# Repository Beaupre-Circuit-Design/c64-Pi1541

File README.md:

# Pi1541-Hat

# Introduction

An open-source Raspberry-Pi Hat for the [Pi1541 firmware](https://cbm-pi1541.firebaseapp.com/). The Hat is divided into two small PCB, the mainboard with the connectors and support logic, and the control board.  They can be assembled together in one unit, or separatly to fit your choice of enclosure.

# Compatibility

The Hat should be compatible with all 40-pins Raspberry Pi supported by the Pi1541 project. That said, i've only tested it with a Raspberry-Pi Zero 2W.

# Configuration

## Rasperry-Pi Zero/2/3.

Follow the instructions of the official firmware. Once your SD created, change the following lines in the file 'options.txt':

    // Uncomment splitIECLines by uncommenting this line. .
	splitIECLines = 1
	// Enable the LCD Display by uncommenting this line. 
	LCDName = ssd1306_128x64
	// Enable KeyboardBrowseLCDScreen by uncommenting theses lines.
	KeyboardBrowseLCDScreen = 1
	i2cBusMaster = 0
	// Disabling GraphIEC for more stability and compatibility with fastloaders by commenting this line.
	//GraphIEC = 1

## Rasperry-Pi Zero 2W.

Follow the instructions of the [c64-Pi1541-Zero2W-Firmware]([Firmware/](https://github.com/Beaupre-Circuit-Design/c64-Pi1541-Zero2W-Firmware)) Github repository.

# Components and assembly

[Gerbers files](Gerbers/) and SMD assembly files are available for uploading to your prefered manufacturer (I personnally use JLCPCB).  The mainboard use SMT parts (except for the headers) while the control board use through-hole components. Refer to the [Bill of Materials](Pi1541-BOM.xlsx) Excel sheet for a complete list of needed components.

# Licence

This work is licensed under the Creative Commons Attribution-NonCommercial-ShareAlike 4.0 International License. To view a copy of this license, visit http://creativecommons.org/licenses/by-nc-sa/4.0/ or send a letter to Creative Commons, PO Box 1866, Mountain View, CA 94042, USA.

# Revision History

|Revision  |Description                    |
|:--------:|-------------------------------|
|1.0       |Initial prototype              |

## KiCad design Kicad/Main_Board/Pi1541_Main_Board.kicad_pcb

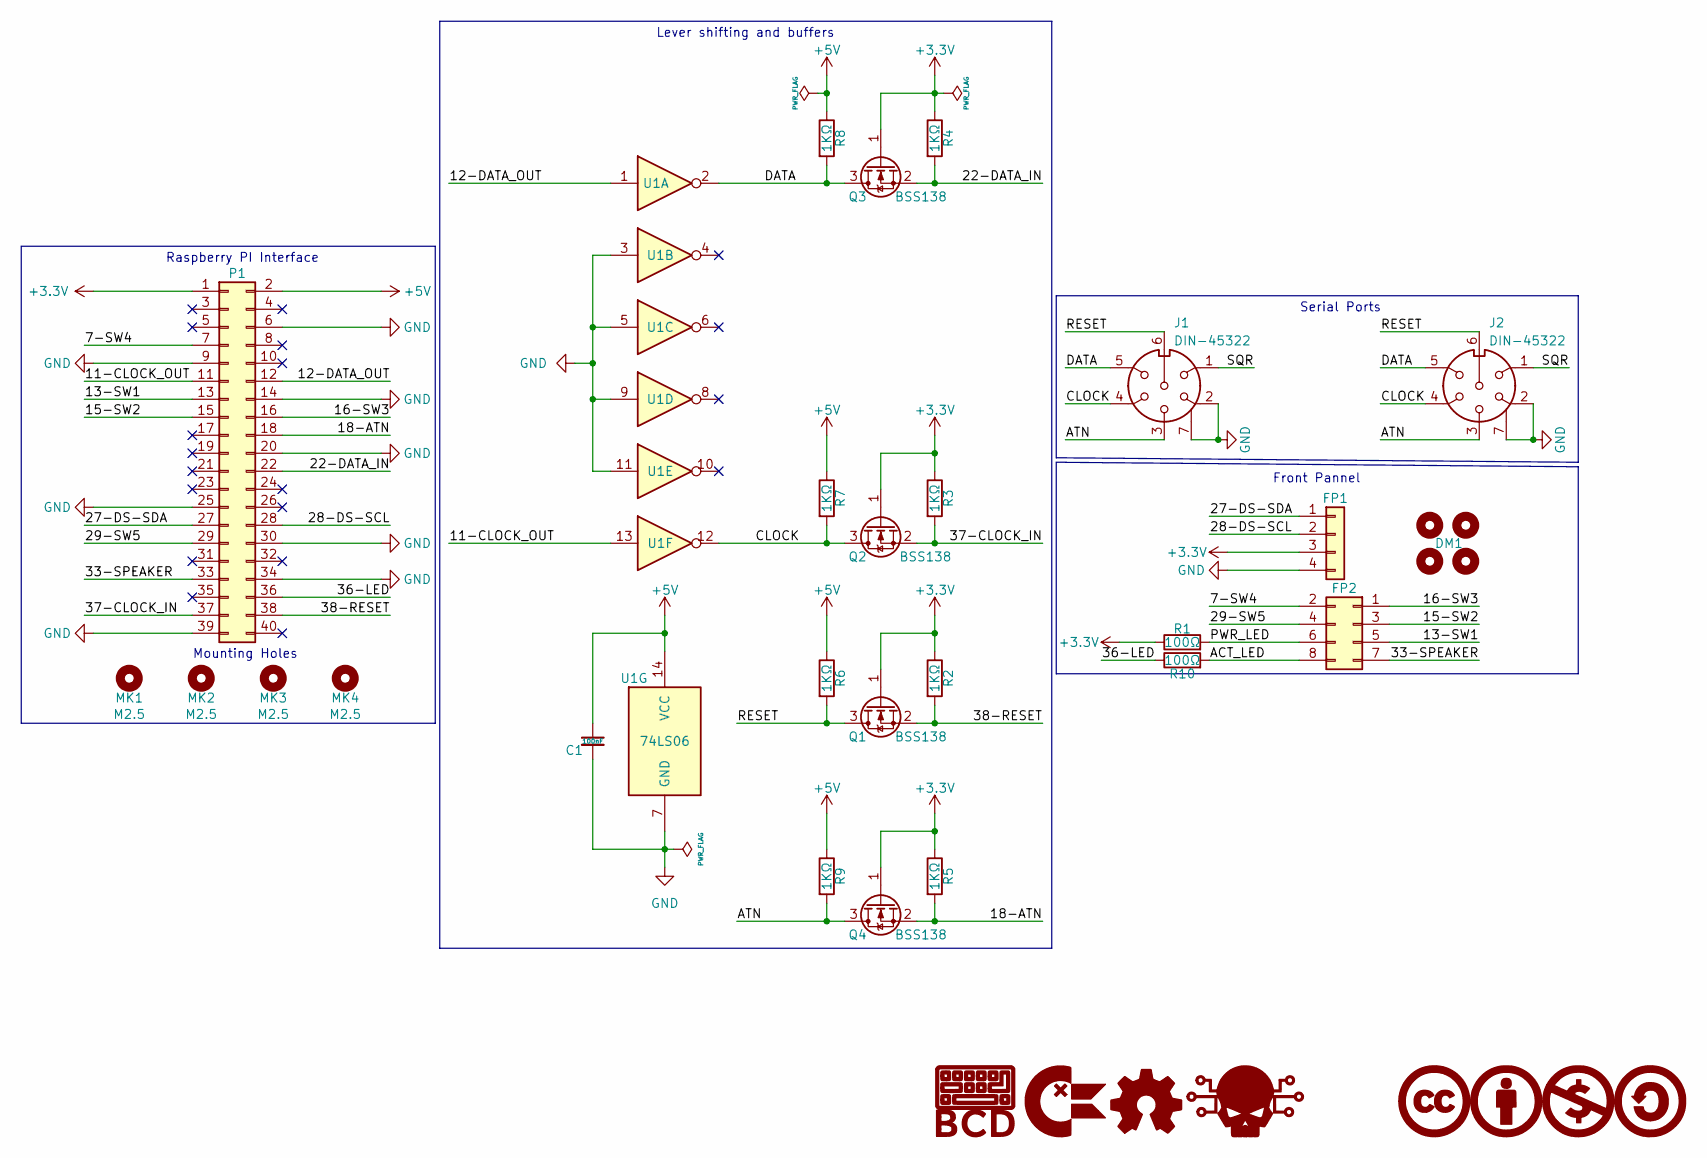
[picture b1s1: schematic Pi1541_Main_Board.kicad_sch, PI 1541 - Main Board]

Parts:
C1: 100nF; C_0805_2012Metric; Mfr.Part CL21C101JBANNNC; LCSC C1790
DM1: 128x64_I2C_OLED_Mounting_Holes; 128x64 I2C OLED Mounting Holes
FP1: Conn_01x04_Counter_Clockwise; PinSocket_1x04_P2.54mm_Vertical; Mfr.Part C2718488; LCSC C2718488
FP2: Conn_02x04_Counter_Clockwise; PinSocket_2x04_P2.54mm_Vertical; Mfr.Part B-2200S08P-B120; LCSC C124422
G1: BCD_Logo; BCD_Logo_5mm
G2: ChickenLips; ChickenLips_5mm
G3: OpenSource_Hardware; Open_Source_Hardware_5mm
G4: Skull; Skull_5mm
G5: CreativeCommons; CreativeCommons_5mm
G6: CreativeCommons_Attribution; CreativeCommons_Attribution_5mm
G7: CreativeCommons_NonCommercial; CreativeCommons_NonCommercial_5mm
G8: CreativeCommons_ShareAlike; CreativeCommons_ShareAlike_5mm
J1, J2: DIN-45322; DIN_45322
MK1, MK2, MK3, MK4: M2.5; MountingHole_2.7mm_M2.5
P1: Conn_02x20_Odd_Even; PinSocket_2x20_P2.54mm_Vertical; Mfr.Part C50982; LCSC C50982
Q1, Q2, Q3, Q4: BSS138; SOT-23; Mfr.Part BSS138; LCSC C112239
R1, R10: 100Ω; R_0805_2012Metric; Mfr.Part 0805W8F1000T5E; LCSC C17408
R2, R3, R4, R5, R6, R7, R8, R9: 1KΩ; R_0805_2012Metric; Mfr.Part 0805W8F1001T5E; LCSC C17513
U1: 74LS06; SOIC-14_3.9x8.7mm_P1.27mm; Mfr.Part SN74LS06DR; LCSC C113682

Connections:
+3V3: FP1.3, P1.1, Q1.1 (G), Q2.1 (G), Q3.1 (G), Q4.1 (G), R1.1, R2.1, R3.1, R4.1, R5.1
+5V: C1.1, P1.2, R6.1, R7.1, R8.1, R9.1, U1.14 (VCC)
/7-SW4: FP2.2, P1.7
/11-CLOCK_OUT: P1.11, U1.13
/12-DATA_OUT: P1.12, U1.1
/13-SW1: FP2.5, P1.13
/15-SW2: FP2.3, P1.15
/16-SW3: FP2.1, P1.16
/18-ATN: P1.18, Q4.2 (S), R5.2
/22-DATA_IN: P1.22, Q3.2 (S), R4.2
/27-DS-SDA: FP1.1, P1.27
/28-DS-SCL: FP1.2, P1.28
/29-SW5: FP2.4, P1.29
/33-SPEAKER: FP2.7, P1.33
/36-LED: P1.36, R10.1
/37-CLOCK_IN: P1.37, Q2.2 (S), R3.2
/38-RESET: P1.38, Q1.2 (S), R2.2
/ACT_LED: FP2.8, R10.2
/ATN: J1.3, J2.3, Q4.3 (D), R9.2
/CLOCK: J1.4, J2.4, Q2.3 (D), R7.2, U1.12
/DATA: J1.5, J2.5, Q3.3 (D), R8.2, U1.2
/PWR_LED: FP2.6, R1.2
/RESET: J1.6, J2.6, Q1.3 (D), R6.2
/SQR: J1.1, J2.1
GND: C1.2, FP1.4, J1.2, J1.7, J2.2, J2.7, P1.6, P1.9, P1.14, P1.20, P1.25, P1.30, P1.34, P1.39, U1.3, U1.5, U1.7 (GND), U1.9, U1.11

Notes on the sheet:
Front Pannel
Serial Ports
Mounting Holes
Raspberry PI Interface
Lever shifting and buffers

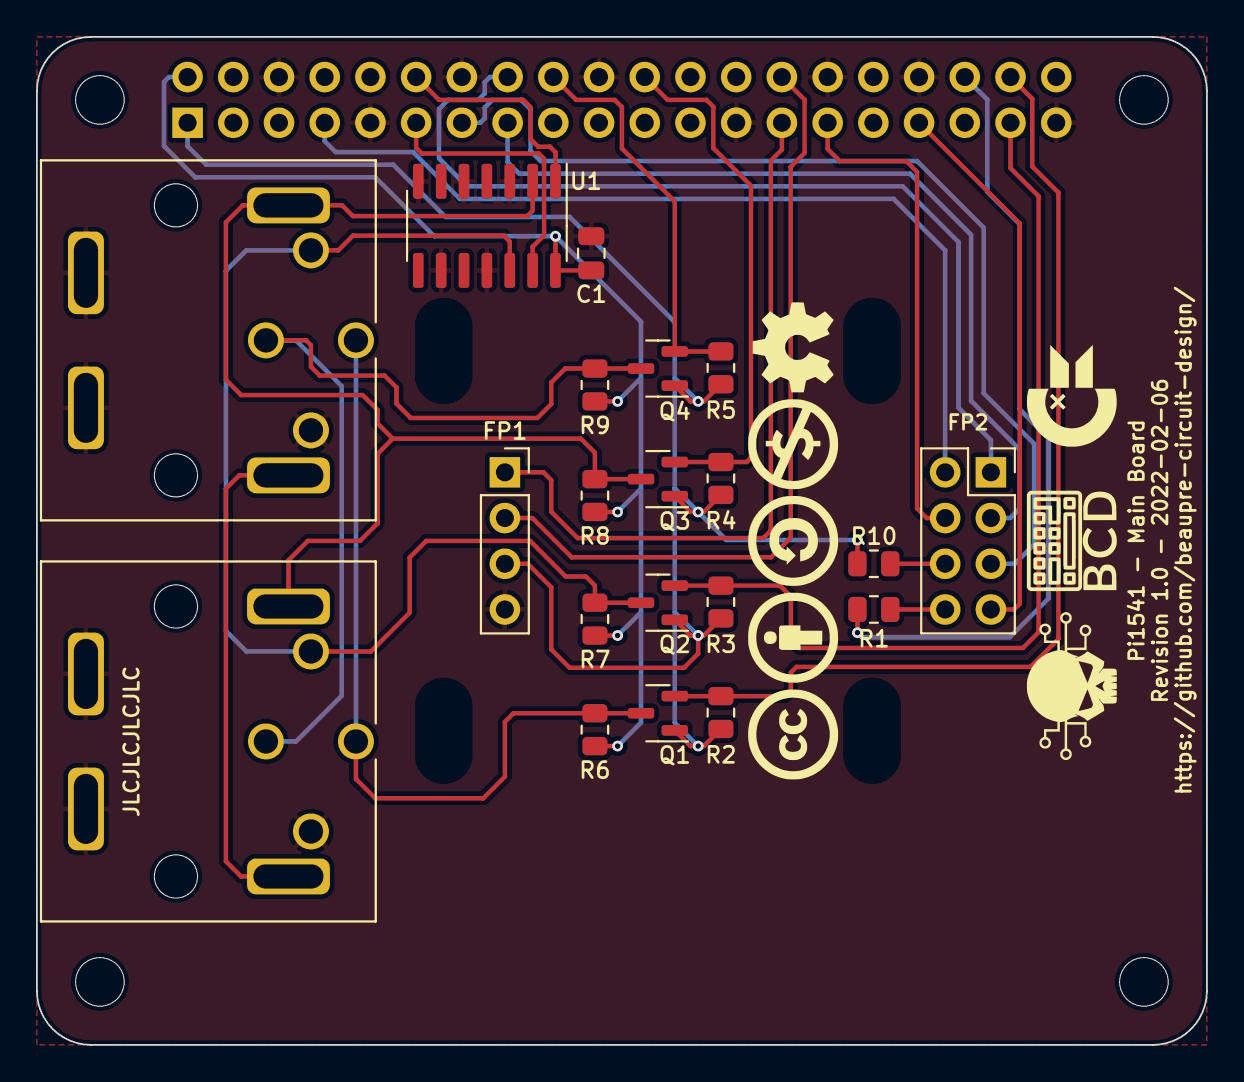
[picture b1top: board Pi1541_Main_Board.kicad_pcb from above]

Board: 2 copper layers, 65.0 x 56.0 mm, 34 parts (1 on the bottom side), 25 nets.

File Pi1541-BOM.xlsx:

Ref | Value | Footprint | Datasheet | Manufacturer | Mfr.Part | LCSC | Digikey | AliExpress | Notes
C1 | 100nF | Capacitor_SMD:C_0805_2012Metric | https://datasheet.lcsc.com/lcsc/1810241824_Samsung-Electro-M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 | Samsung Electro-Mechanics | CL21C101JBANNNC | C1790 | 1276-1014-1-ND
FP1 | Conn_01x04_Counter_Clockwise | Connector_PinSocket_2.54mm:PinSocket_1x04_P2.54mm_Vertical | https://datasheet.lcsc.com/lcsc/2103011236_BOOMELE-Boom-Prec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 | Boom Precision Elec | C2718488 | C2718488 | S7037-ND
FP2 | Conn_02x04_Counter_Clockwise | Connector_PinSocket_2.54mm:PinSocket_2x04_P2.54mm_Vertical | https://datasheet.lcsc.com/lcsc/1810221610_Ckmtw-Shenzhen-Ca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 | Shenzhen Cankemeng | B-2200S08P-B120 | C124422 | S7107-ND
J1 | DIN-45322 | DIN_45322:DIN_45322 | https://www.aliexpress.com/item/1005001265863686.html | AliExpress |  |  |  | 1005001265863680
J2 | DIN-45322 | DIN_45322:DIN_45322 | https://www.aliexpress.com/item/1005001265863686.html | AliExpress |  |  |  | 1005001265863680
P1 | Conn_02x20_Odd_Even | Connector_PinSocket_2.54mm:PinSocket_2x20_P2.54mm_Vertical | https://datasheet.lcsc.com/lcsc/1811111512_BOOMELE-Boom-Prec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 | Boom Precision Elec | C50982 | C50982 | S7123-ND
Q1 | BSS138 | Package_TO_SOT_SMD:SOT-23 | https://datasheet.lcsc.com/lcsc/1811101310_Shikues-BSS138_C1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 | Shikues | BSS138 | C112239 | BSS138CT-ND
Q2 | BSS138 | Package_TO_SOT_SMD:SOT-23 | https://datasheet.lcsc.com/lcsc/1811101310_Shikues-BSS138_C1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 | Shikues | BSS138 | C112239 | BSS138CT-ND
Q3 | BSS138 | Package_TO_SOT_SMD:SOT-23 | https://datasheet.lcsc.com/lcsc/1811101310_Shikues-BSS138_C1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 | Shikues | BSS138 | C112239 | BSS138CT-ND
Q4 | BSS138 | Package_TO_SOT_SMD:SOT-23 | https://datasheet.lcsc.com/lcsc/1811101310_Shikues-BSS138_C1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 | Shikues | BSS138 | C112239 | BSS138CT-ND
R1 | 100Ω | Resistor_SMD:R_0805_2012Metric | https://datasheet.lcsc.com/lcsc/2110251730_UNI-ROYAL-Uniroya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 | UNI-ROYAL(Uniroyal Elec) | 0805W8F1000T5E | C17408 | 311-100CRCT-ND
R2 | 1KΩ | Resistor_SMD:R_0805_2012Metric | https://datasheet.lcsc.com/lcsc/2110251730_UNI-ROYAL-Uniroya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 | UNI-ROYAL(Uniroyal Elec) | 0805W8F1001T5E | C17513 | 311-1.00KCRCT-ND
R3 | 1KΩ | Resistor_SMD:R_0805_2012Metric | https://datasheet.lcsc.com/lcsc/2110251730_UNI-ROYAL-Uniroya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 | UNI-ROYAL(Uniroyal Elec) | 0805W8F1001T5E | C17513 | 311-1.00KCRCT-ND
R4 | 1KΩ | Resistor_SMD:R_0805_2012Metric | https://datasheet.lcsc.com/lcsc/2110251730_UNI-ROYAL-Uniroya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 | UNI-ROYAL(Uniroyal Elec) | 0805W8F1001T5E | C17513 | 311-1.00KCRCT-ND
R5 | 1KΩ | Resistor_SMD:R_0805_2012Metric | https://datasheet.lcsc.com/lcsc/2110251730_UNI-ROYAL-Uniroya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 | UNI-ROYAL(Uniroyal Elec) | 0805W8F1001T5E | C17513 | 311-1.00KCRCT-ND
R6 | 1KΩ | Resistor_SMD:R_0805_2012Metric | https://datasheet.lcsc.com/lcsc/2110251730_UNI-ROYAL-Uniroya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 | UNI-ROYAL(Uniroyal Elec) | 0805W8F1001T5E | C17513 | 311-1.00KCRCT-ND
R7 | 1KΩ | Resistor_SMD:R_0805_2012Metric | https://datasheet.lcsc.com/lcsc/2110251730_UNI-ROYAL-Uniroya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 | UNI-ROYAL(Uniroyal Elec) | 0805W8F1001T5E | C17513 | 311-1.00KCRCT-ND
R8 | 1KΩ | Resistor_SMD:R_0805_2012Metric | https://datasheet.lcsc.com/lcsc/2110251730_UNI-ROYAL-Uniroya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 | UNI-ROYAL(Uniroyal Elec) | 0805W8F1001T5E | C17513 | 311-1.00KCRCT-ND
R9 | 1KΩ | Resistor_SMD:R_0805_2012Metric | https://datasheet.lcsc.com/lcsc/2110251730_UNI-ROYAL-Uniroya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 | UNI-ROYAL(Uniroyal Elec) | 0805W8F1001T5E | C17513 | 311-1.00KCRCT-ND
R10 | 100Ω | Resistor_SMD:R_0805_2012Metric | https://datasheet.lcsc.com/lcsc/2110251730_UNI-ROYAL-Uniroya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 | UNI-ROYAL(Uniroyal Elec) | 0805W8F1000T5E | C17408 | 311-100CRCT-ND
U1 | 74LS06 | Package_SO:SOIC-14_3.9x8.7mm_P1.27mm | https://datasheet.lcsc.com/lcsc/1810151621_Texas-Instruments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 | Texas Instruments | SN74LS06DR | C113682 | 296-14876-1-ND

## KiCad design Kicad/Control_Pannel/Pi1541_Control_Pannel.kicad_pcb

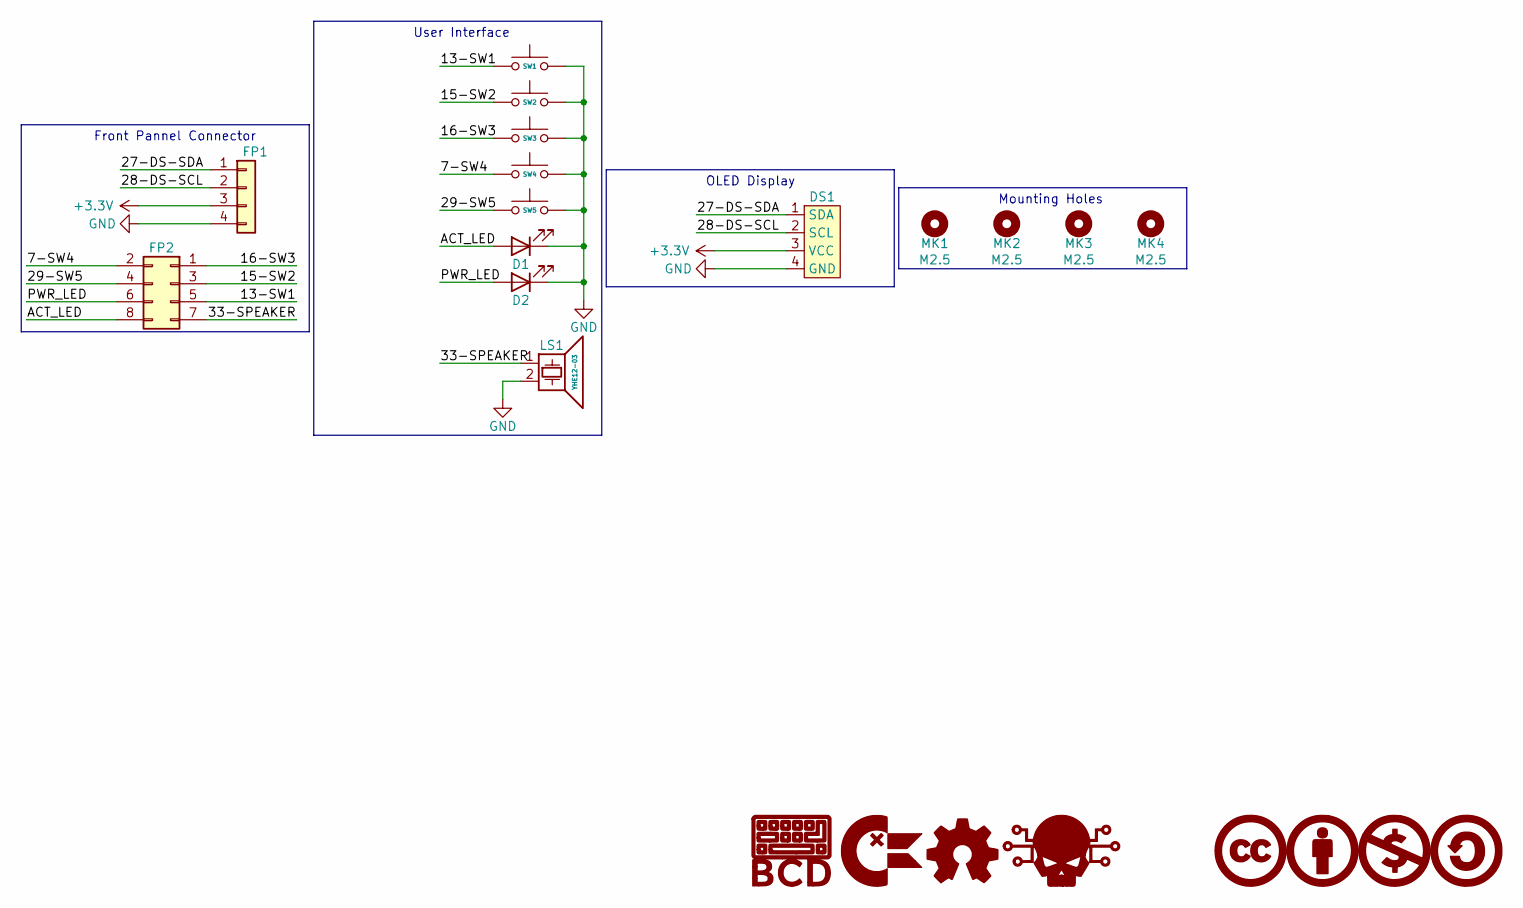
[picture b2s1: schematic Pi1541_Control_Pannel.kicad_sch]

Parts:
D1: RED LED; LED_D5.0mm; Mfr.Part 333-2SURD/S530-A3; LCSC C87271
D2: GREEN LED; LED_D5.0mm; Mfr.Part 333-2SYGD/S530-E2; LCSC C88163
DS1: 128x64_I2C_OLED_Display; 128x64 I2C OLED Display
FP1: Conn_01x04_Counter_Clockwise; PinHeader_1x04_P2.54mm_Vertical; Mfr.Part B-2100S04P-A110; LCSC C124378
FP2: Conn_02x04_Counter_Clockwise; PinHeader_2x04_P2.54mm_Vertical; Mfr.Part B-2100S08P-B110; LCSC C124386
G1: BCD_Logo; BCD_Logo_5mm
G2: ChickenLips; ChickenLips_5mm
G3: OpenSource_Hardware; Open_Source_Hardware_5mm
G4: Skull; Skull_5mm
G5: CreativeCommons; CreativeCommons_5mm
G6: CreativeCommons_Attribution; CreativeCommons_Attribution_5mm
G7: CreativeCommons_NonCommercial; CreativeCommons_NonCommercial_5mm
G8: CreativeCommons_ShareAlike; CreativeCommons_ShareAlike_5mm
LS1: YHE12-03; Buzzer_12x9.5RM7.6
MK1, MK2, MK3, MK4: M2.5; MountingHole_2.7mm_M2.5
SW1, SW2, SW3, SW4, SW5: SW_Push; SW_PUSH_6mm

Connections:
+3V3: DS1.3 (VCC), FP1.3
/7-SW4: FP2.2, SW4.1
/13-SW1: FP2.5, SW1.1
/15-SW2: FP2.3, SW2.1
/16-SW3: FP2.1, SW3.1
/27-DS-SDA: DS1.1 (SDA), FP1.1
/28-DS-SCL: DS1.2 (SCL), FP1.2
/29-SW5: FP2.4, SW5.1
/33-SPEAKER: FP2.7, LS1.1
/ACT_LED: D1.2 (A), FP2.8
/PWR_LED: D2.2 (A), FP2.6
GND: D1.1 (K), D2.1 (K), DS1.4 (GND), FP1.4, LS1.2, SW1.2, SW2.2, SW3.2, SW4.2, SW5.2

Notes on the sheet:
Front Pannel Connector
Mounting Holes
OLED Display
User Interface

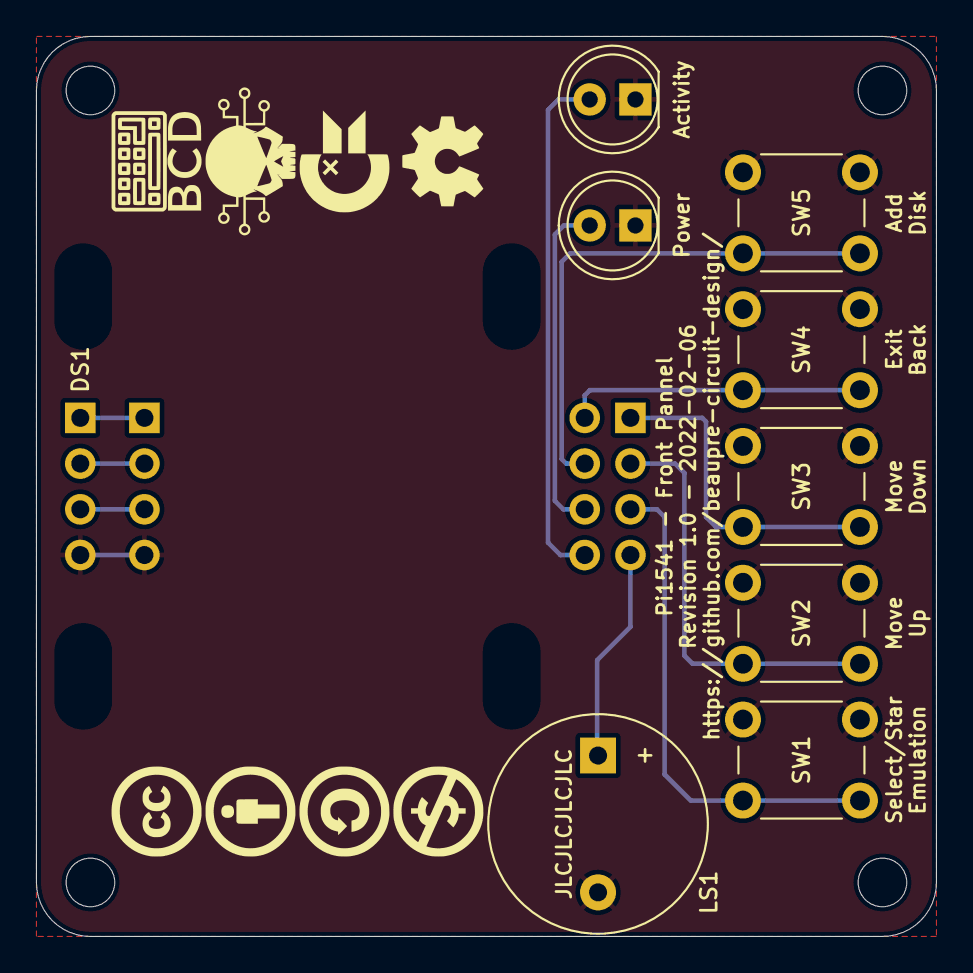
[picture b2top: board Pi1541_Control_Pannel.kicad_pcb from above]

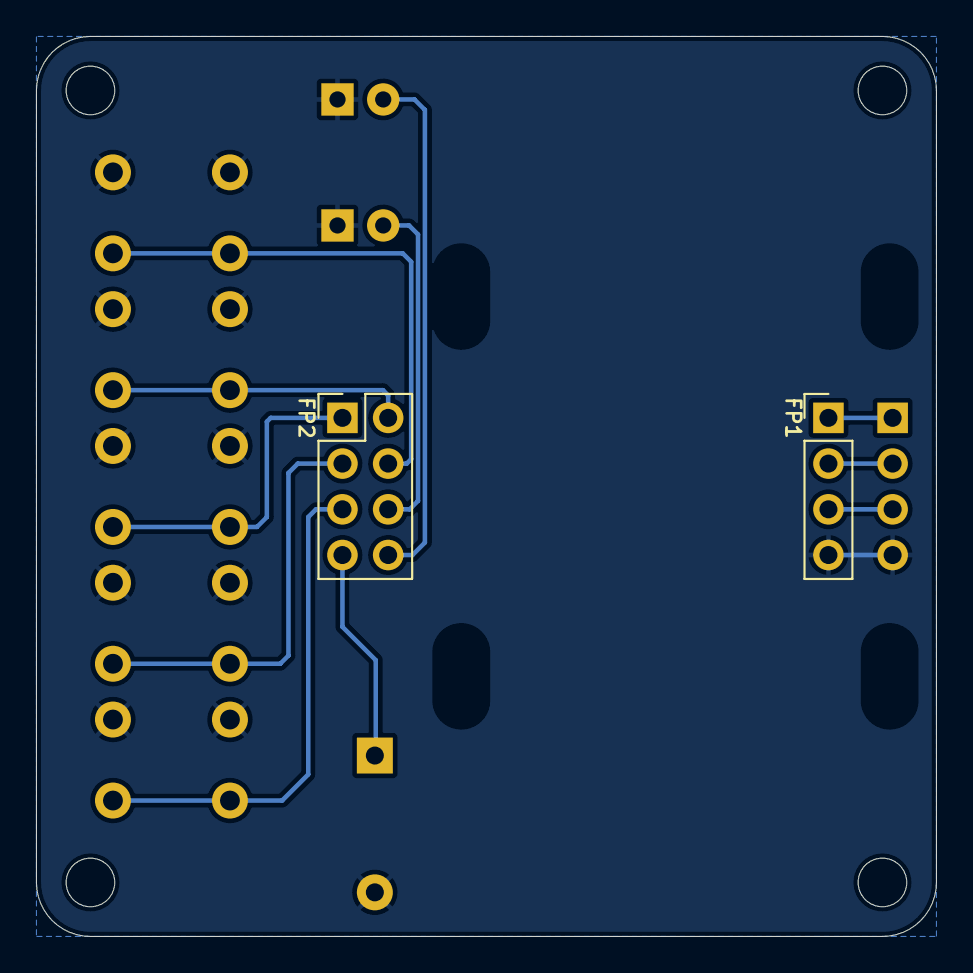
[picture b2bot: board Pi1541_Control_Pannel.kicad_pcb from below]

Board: 2 copper layers, 50.0 x 50.0 mm, 23 parts (2 on the bottom side), 12 nets.

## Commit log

2022-03-16 Initial Commit.
